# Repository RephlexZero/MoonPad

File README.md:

KiCAD design files for the RP2040 based analogue 2k keyboard.

Online viewing available here:

https://kicanvas.org/?github=https%3A%2F%2Fgithub.com%2FRephlexZero%2FMoonPad%2Ftree%2Fmaster

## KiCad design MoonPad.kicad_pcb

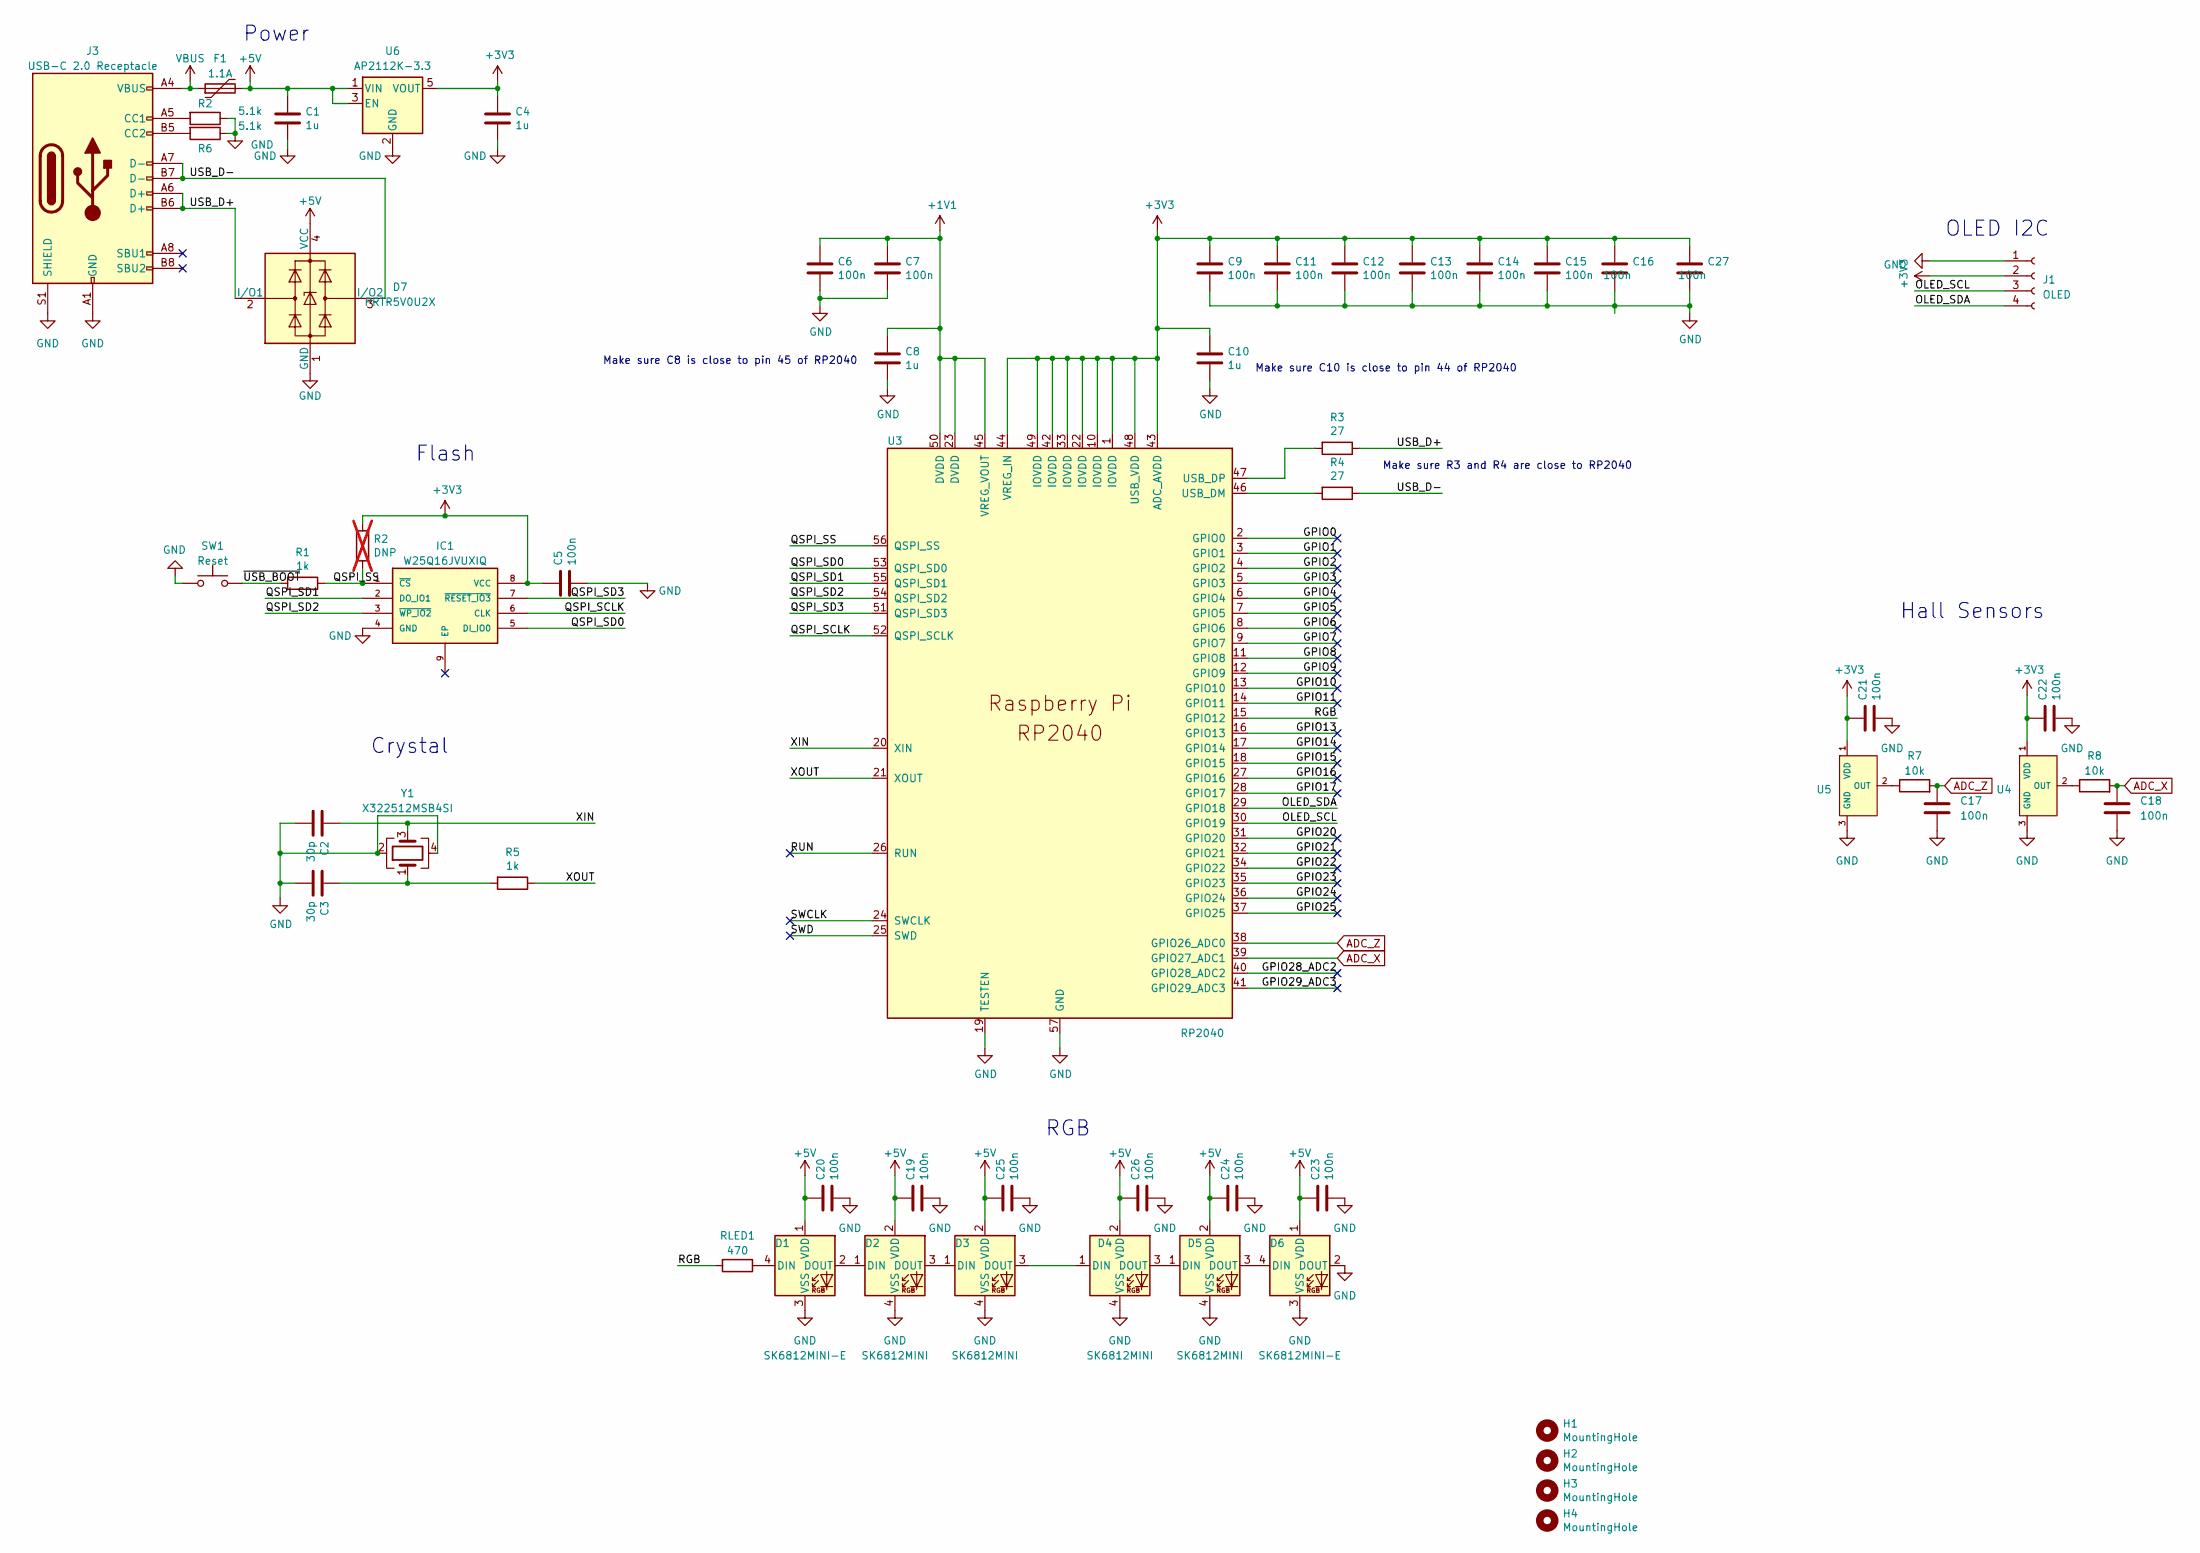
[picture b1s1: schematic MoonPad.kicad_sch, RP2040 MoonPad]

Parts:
C1, C4: 1u; C_0805_2012Metric; LCSC Part C28323
C2, C3: 30p; C_0402_1005Metric; LCSC C1570
C5, C6, C7, C9, C11, C12, C13, C14, C15, C16, C17, C18, C19, C20, C21, C22, C23, C24, C25, C26, C27: 100n; C_0402_1005Metric; LCSC C1525
C8, C10: 1u; C_0402_1005Metric; LCSC C52923
D1, D6: SK6812MINI-E; MX_SK6812MINI-E_REV; LCSC C5378731
D2, D3, D4, D5: SK6812MINI; LED_SK6812MINI-B-012_3.7x3.5mm_P1.1mm; LCSC C2886570
D7: PRTR5V0U2X; SOT-143; LCSC C2827688
F1: 1.1A; Fuse_1206_3216Metric; LCSC C2760273
H1, H2, H3, H4: MountingHole; MountingHole_2.2mm_M2
IC1: W25Q16JVUXIQ; SON50P300X200X60-9N; MANUFACTURER_PART_NUMBER W25Q16JVUXIQ; LCSC C2843335
J1: OLED; PinHeader_1x04_P2.54mm_Vertical
J3: USB-C 2.0 Receptacle; USB_C_Receptacle_HRO_TYPE-C-31-M-12; LCSC C165948
R1, R5: 1k; R_0402_1005Metric; LCSC C11702
R2: DNP; C_0402_1005Metric; LCSC C25905; not fitted
R3, R4: 27; R_0402_1005Metric; LCSC C25100
R6: 5.1k; R_0402_1005Metric; LCSC C25905
R7, R8: 10k; R_0402_1005Metric; LCSC C25744
RLED1: 470; R_0402_1005Metric; LCSC Part C2828857
SW1: Reset; SW_SPST_TL3342; LCSC Part C115351
U3: RP2040; RP2040-QFN-56; LCSC C2040
U4, U5: SLSS49E-3; SOT-23; LCSC C2904393
U6: AP2112K-3.3; SOT-23-5; LCSC C51118
Y1: X322512MSB4SI; Crystal_SMD_3225-4Pin_3.2x2.5mm; LCSC C9002

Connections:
+1V1: C6.1, C7.1, C8.1, U3.23 (DVDD), U3.45 (VREG_VOUT), U3.50 (DVDD)
+5V: C1.1, C19.1, C20.1, C23.1, C24.1, C25.1, C26.1, D1.1 (VDD), D2.2 (VDD), D3.2 (VDD), D4.2 (VDD), D5.2 (VDD), D6.1 (VDD), D7.4 (VCC), F1.2, U6.1 (VIN), U6.3 (EN)
/GPIO0: U3.2 (GPIO0)
/GPIO1: U3.3 (GPIO1)
/GPIO2: U3.4 (GPIO2)
/GPIO3: U3.5 (GPIO3)
/GPIO4: U3.6 (GPIO4)
/GPIO5: U3.7 (GPIO5)
/GPIO6: U3.8 (GPIO6)
/GPIO7: U3.9 (GPIO7)
/GPIO8: U3.11 (GPIO8)
/GPIO9: U3.12 (GPIO9)
/GPIO10: U3.13 (GPIO10)
/GPIO11: U3.14 (GPIO11)
/GPIO13: U3.16 (GPIO13)
/GPIO14: U3.17 (GPIO14)
/GPIO15: U3.18 (GPIO15)
/GPIO16: U3.27 (GPIO16)
/GPIO17: U3.28 (GPIO17)
/GPIO20: U3.31 (GPIO20)
/GPIO21: U3.32 (GPIO21)
/GPIO22: U3.34 (GPIO22)
/GPIO23: U3.35 (GPIO23)
/GPIO24: U3.36 (GPIO24)
/GPIO25: U3.37 (GPIO25)
/GPIO28_ADC2: U3.40 (GPIO28_ADC2)
/GPIO29_ADC3: U3.41 (GPIO29_ADC3)
/OLED_SCL: J1.3, U3.30 (GPIO19)
/OLED_SDA: J1.4, U3.29 (GPIO18)
/QSPI_SCLK: IC1.6 (CLK), U3.52 (QSPI_SCLK)
/QSPI_SD0: IC1.5 (DI_IO0), U3.53 (QSPI_SD0)
/QSPI_SD1: IC1.2 (DO_IO1), U3.55 (QSPI_SD1)
/QSPI_SD2: IC1.3 (~WP_IO2), U3.54 (QSPI_SD2)
/QSPI_SD3: IC1.7 (~RESET_IO3), U3.51 (QSPI_SD3)
/RGB: RLED1.2, U3.15 (GPIO12)
/RUN: U3.26 (RUN)
/SWCLK: U3.24 (SWCLK)
/SWD: U3.25 (SWD)
/USB_D+: D7.2 (I/O1), J3.A6 (D+), J3.B6 (D+), R3.1
/USB_D-: D7.3 (I/O2), J3.A7 (D-), J3.B7 (D-), R4.1
/XIN: C2.1, U3.20 (XIN), Y1.3
/XOUT: R5.1, U3.21 (XOUT)
/~USB_BOOT: R1.2, SW1.2
ADC_X: C18.1, R8.2, U3.39 (GPIO27_ADC1)
ADC_Z: C17.1, R7.2, U3.38 (GPIO26_ADC0)
unnamed: C3.1, R5.2, Y1.1
unnamed: D1.4 (DIN), RLED1.1
unnamed: D1.2 (DOUT), D2.1 (DIN)
unnamed: D2.3 (DOUT), D3.1 (DIN)
unnamed: D3.3 (DOUT), D4.1 (DIN)
unnamed: D4.3 (DOUT), D5.1 (DIN)
unnamed: D5.3 (DOUT), D6.4 (DIN)
unnamed: J3.B5 (CC2), R6.2
unnamed: R4.2, U3.46 (USB_DM)
unnamed: R3.2, U3.47 (USB_DP)
unnamed: R8.1, U4.2 (OUT)
unnamed: R7.1, U5.2 (OUT)
VBUS: F1.1, J3.A4 (VBUS), J3.A9 (VBUS), J3.B4 (VBUS), J3.B9 (VBUS)

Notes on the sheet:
Flash
OLED I2C
Power
Make sure R3 and R4 are close to RP2040
Make sure C10 is close to pin 44 of RP2040
Hall Sensors
Crystal
RGB
Make sure C8 is close to pin 45 of RP2040

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
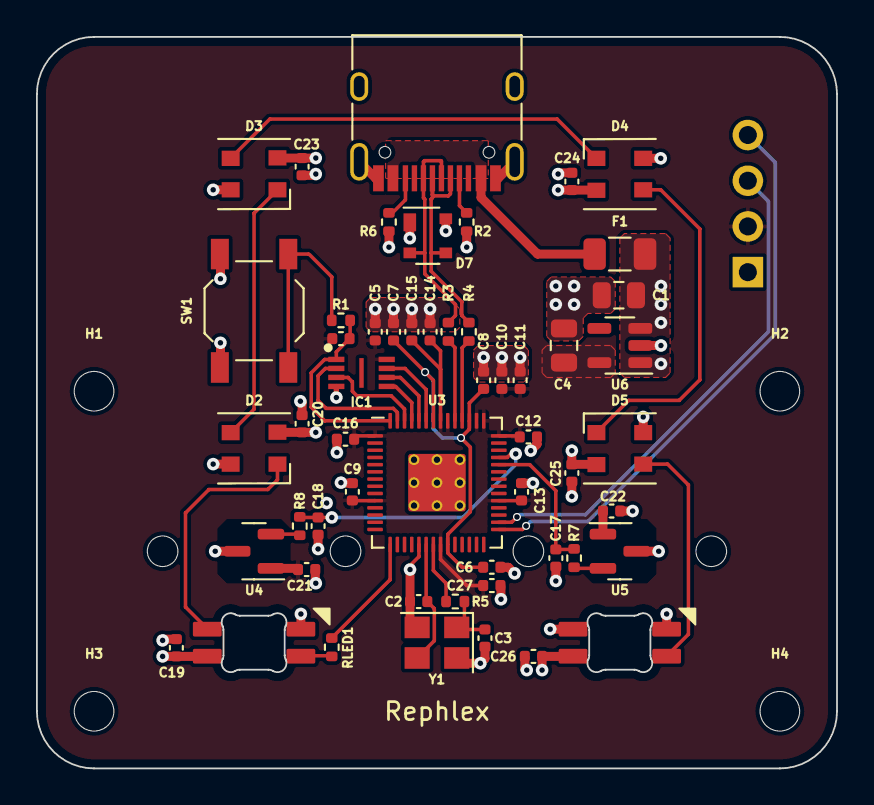
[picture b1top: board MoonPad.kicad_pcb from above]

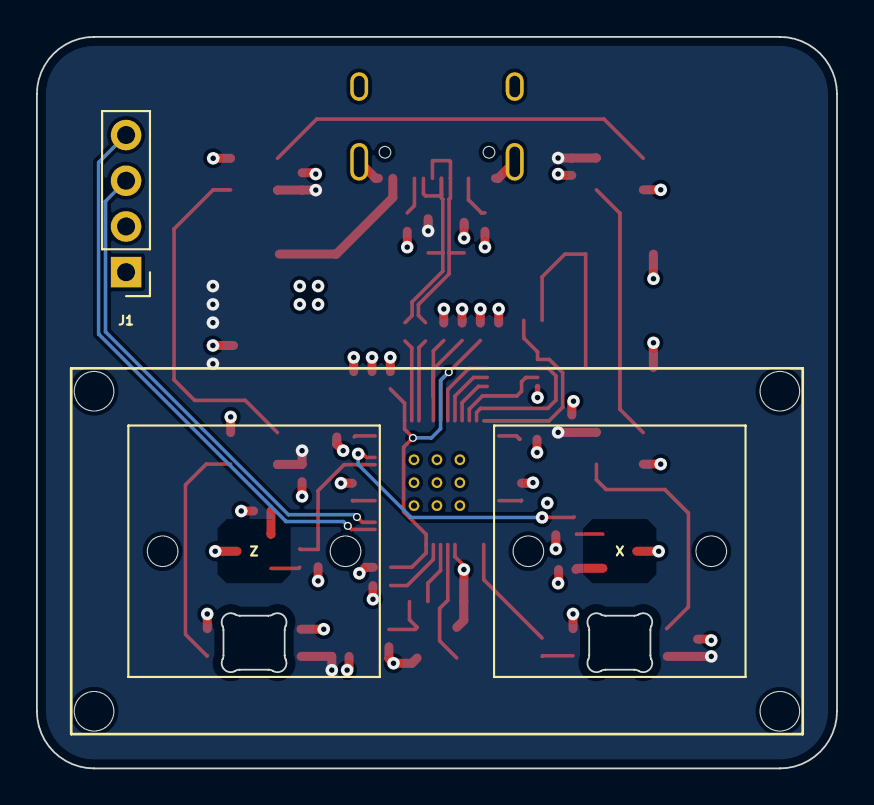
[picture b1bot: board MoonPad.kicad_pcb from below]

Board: 4 copper layers, 44.5 x 40.6 mm, 60 parts (3 on the bottom side), 34 nets.

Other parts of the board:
R9: DNP; C_0402_1005Metric
X: Wooting_1.00u
Z: Wooting_1.00u

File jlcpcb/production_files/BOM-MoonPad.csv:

Comment,Designator,Footprint,LCSC
1k,"R1,R5",R_0402_1005Metric,C11702
100n,"C11,C12,C13,C14,C15,C16,C17,C18,C19,C20,C21,C22,C23,C24,C25,C26,C27,C5,C6,C7,C9",C_0402_1005Metric,C1525
30p,"C2,C3",C_0402_1005Metric,C1570
USB-C 2.0 Receptacle,J3,USB_C_Receptacle_HRO_TYPE-C-31-M-12,C165948
RP2040,U3,RP2040-QFN-56,C2040
27,"R3,R4",R_0402_1005Metric,C25100
470,RLED1,R_0402_1005Metric,C25117
10k,"R7,R8",R_0402_1005Metric,C25744
5.1k,"R2,R6",R_0402_1005Metric,C25905
1.1A,F1,Fuse_1206_3216Metric,C2760273
PRTR5V0U2X,D7,SOT-143,C2827688
1u,"C1,C4",C_0805_2012Metric,C28323
W25Q16JVUXIQ,IC1,SON50P300X200X60-9N,C2843335
SK6812MINI,"D2,D3,D4,D5",LED_SK6812MINI-B-012_3.7x3.5mm_P1.1mm,C2886570
SLSS49E-3,"U4,U5",SOT-23,C2904393
Reset,SW1,SW_SPST_TL3342,C318884
AP2112K-3.3,U6,SOT-23-5,C51118
1u,"C10,C8",C_0402_1005Metric,C52923
SK6812MINI-E,"D1,D6",MX_SK6812MINI-E_REV,C5378731
X322512MSB4SI,Y1,Crystal_SMD_3225-4Pin_3.2x2.5mm,C9002

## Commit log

2023-05-11 Added gerbers and drill files
2023-05-11 Migrate manufacturing files to seperate folder
2023-05-12 Added ESD Protection
2023-05-12 Added fuse
2023-05-13 Added part numbers, some schema adjustments
2023-05-13 Minor layout changes
2023-05-13 All part numbers added
2023-05-17 Less extended parts
2023-05-17 Fixed libraries
2023-05-18 Edited some 3d. Now sent for manufacturing.
2023-10-17 Cost optimisation + case files
